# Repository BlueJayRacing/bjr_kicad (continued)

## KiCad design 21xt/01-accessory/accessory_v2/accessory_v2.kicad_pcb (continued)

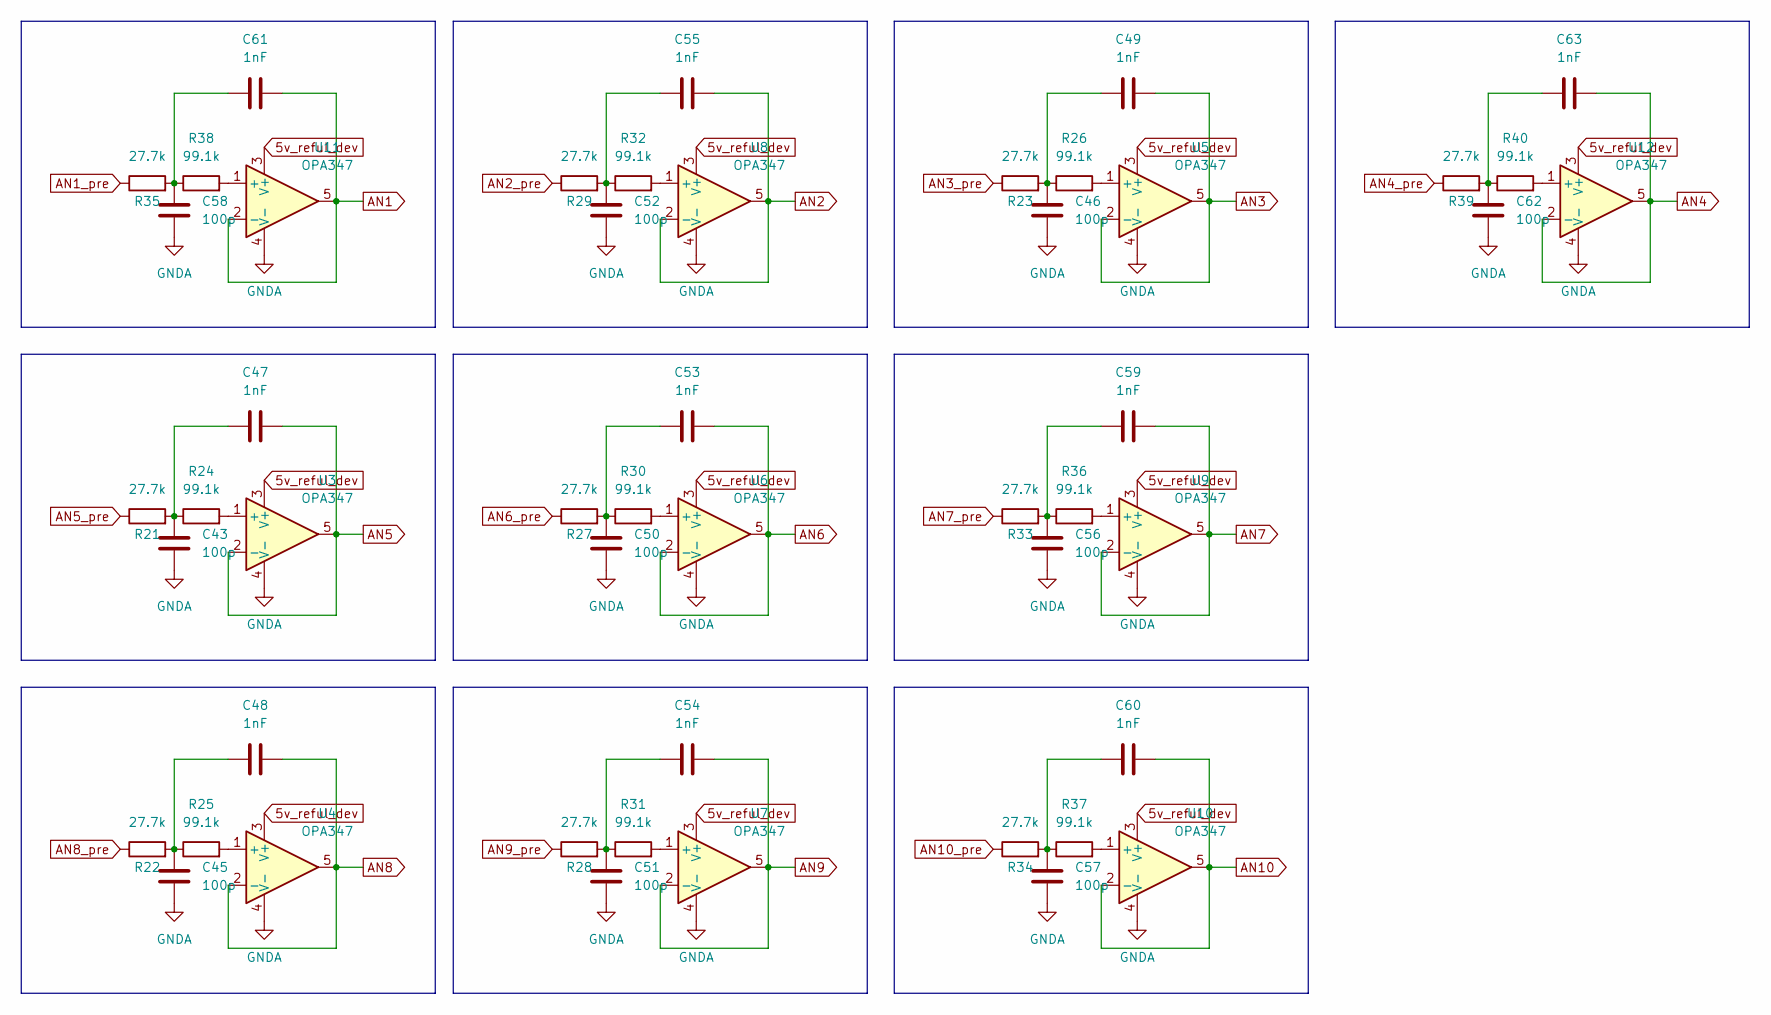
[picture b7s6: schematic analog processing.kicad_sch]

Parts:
C43, C45, C46, C50, C51, C52, C56, C57, C58, C62: 100p; C_0402_1005Metric
C47, C48, C49, C53, C54, C55, C59, C60, C61, C63: 1nF; C_0402_1005Metric
R21, R22, R23, R27, R28, R29, R33, R34, R35, R39: 27.7k; R_0402_1005Metric
R24, R25, R26, R30, R31, R32, R36, R37, R38, R40: 99.1k; R_0402_1005Metric
U3, U4, U5, U6, U7, U8, U9, U10, U11, U12: OPA347; SOT-23-5

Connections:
5v_reful_dev: U3.3 (V+), U4.3 (V+), U5.3 (V+), U6.3 (V+), U7.3 (V+), U8.3 (V+), U9.3 (V+), U10.3 (V+), U11.3 (V+), U12.3 (V+); also elsewhere on the board
AN1: C61.2, U11.2 (-), U11.5; also elsewhere on the board
AN1_pre: R35.1; also elsewhere on the board
AN2: C55.2, U8.2 (-), U8.5; also elsewhere on the board
AN2_pre: R29.1; also elsewhere on the board
AN3: C49.2, U5.2 (-), U5.5; also elsewhere on the board
AN3_pre: R23.1; also elsewhere on the board
AN4: C63.2, U12.2 (-), U12.5; also elsewhere on the board
AN4_pre: R39.1; also elsewhere on the board
AN5: C47.2, U3.2 (-), U3.5; also elsewhere on the board
AN5_pre: R21.1; also elsewhere on the board
AN6: C53.2, U6.2 (-), U6.5; also elsewhere on the board
AN6_pre: R27.1; also elsewhere on the board
AN7: C59.2, U9.2 (-), U9.5; also elsewhere on the board
AN7_pre: R33.1; also elsewhere on the board
AN8: C48.2, U4.2 (-), U4.5; also elsewhere on the board
AN8_pre: R22.1; also elsewhere on the board
AN9: C54.2, U7.2 (-), U7.5; also elsewhere on the board
AN9_pre: R28.1; also elsewhere on the board
AN10: C60.2, U10.2 (-), U10.5; also elsewhere on the board
AN10_pre: R34.1; also elsewhere on the board
unnamed: C43.1, C47.1, R21.2, R24.1
unnamed: C45.1, C48.1, R22.2, R25.1
unnamed: C46.1, C49.1, R23.2, R26.1
unnamed: C50.1, C53.1, R27.2, R30.1
unnamed: C51.1, C54.1, R28.2, R31.1
unnamed: C52.1, C55.1, R29.2, R32.1
unnamed: C56.1, C59.1, R33.2, R36.1
unnamed: C57.1, C60.1, R34.2, R37.1
unnamed: C58.1, C61.1, R35.2, R38.1
unnamed: C62.1, C63.1, R39.2, R40.1
unnamed: R24.2, U3.1 (+)
unnamed: R25.2, U4.1 (+)
unnamed: R26.2, U5.1 (+)
unnamed: R30.2, U6.1 (+)
unnamed: R31.2, U7.1 (+)
unnamed: R32.2, U8.1 (+)
unnamed: R36.2, U9.1 (+)
unnamed: R37.2, U10.1 (+)
unnamed: R38.2, U11.1 (+)
unnamed: R40.2, U12.1 (+)
usb_gnd: C43.2, C45.2, C46.2, C50.2, C51.2, C52.2, C56.2, C57.2, C58.2, C62.2, U3.4 (V-), U4.4 (V-), U5.4 (V-), U6.4 (V-), U7.4 (V-), U8.4 (V-), U9.4 (V-), U10.4 (V-), U11.4 (V-), U12.4 (V-); also elsewhere on the board

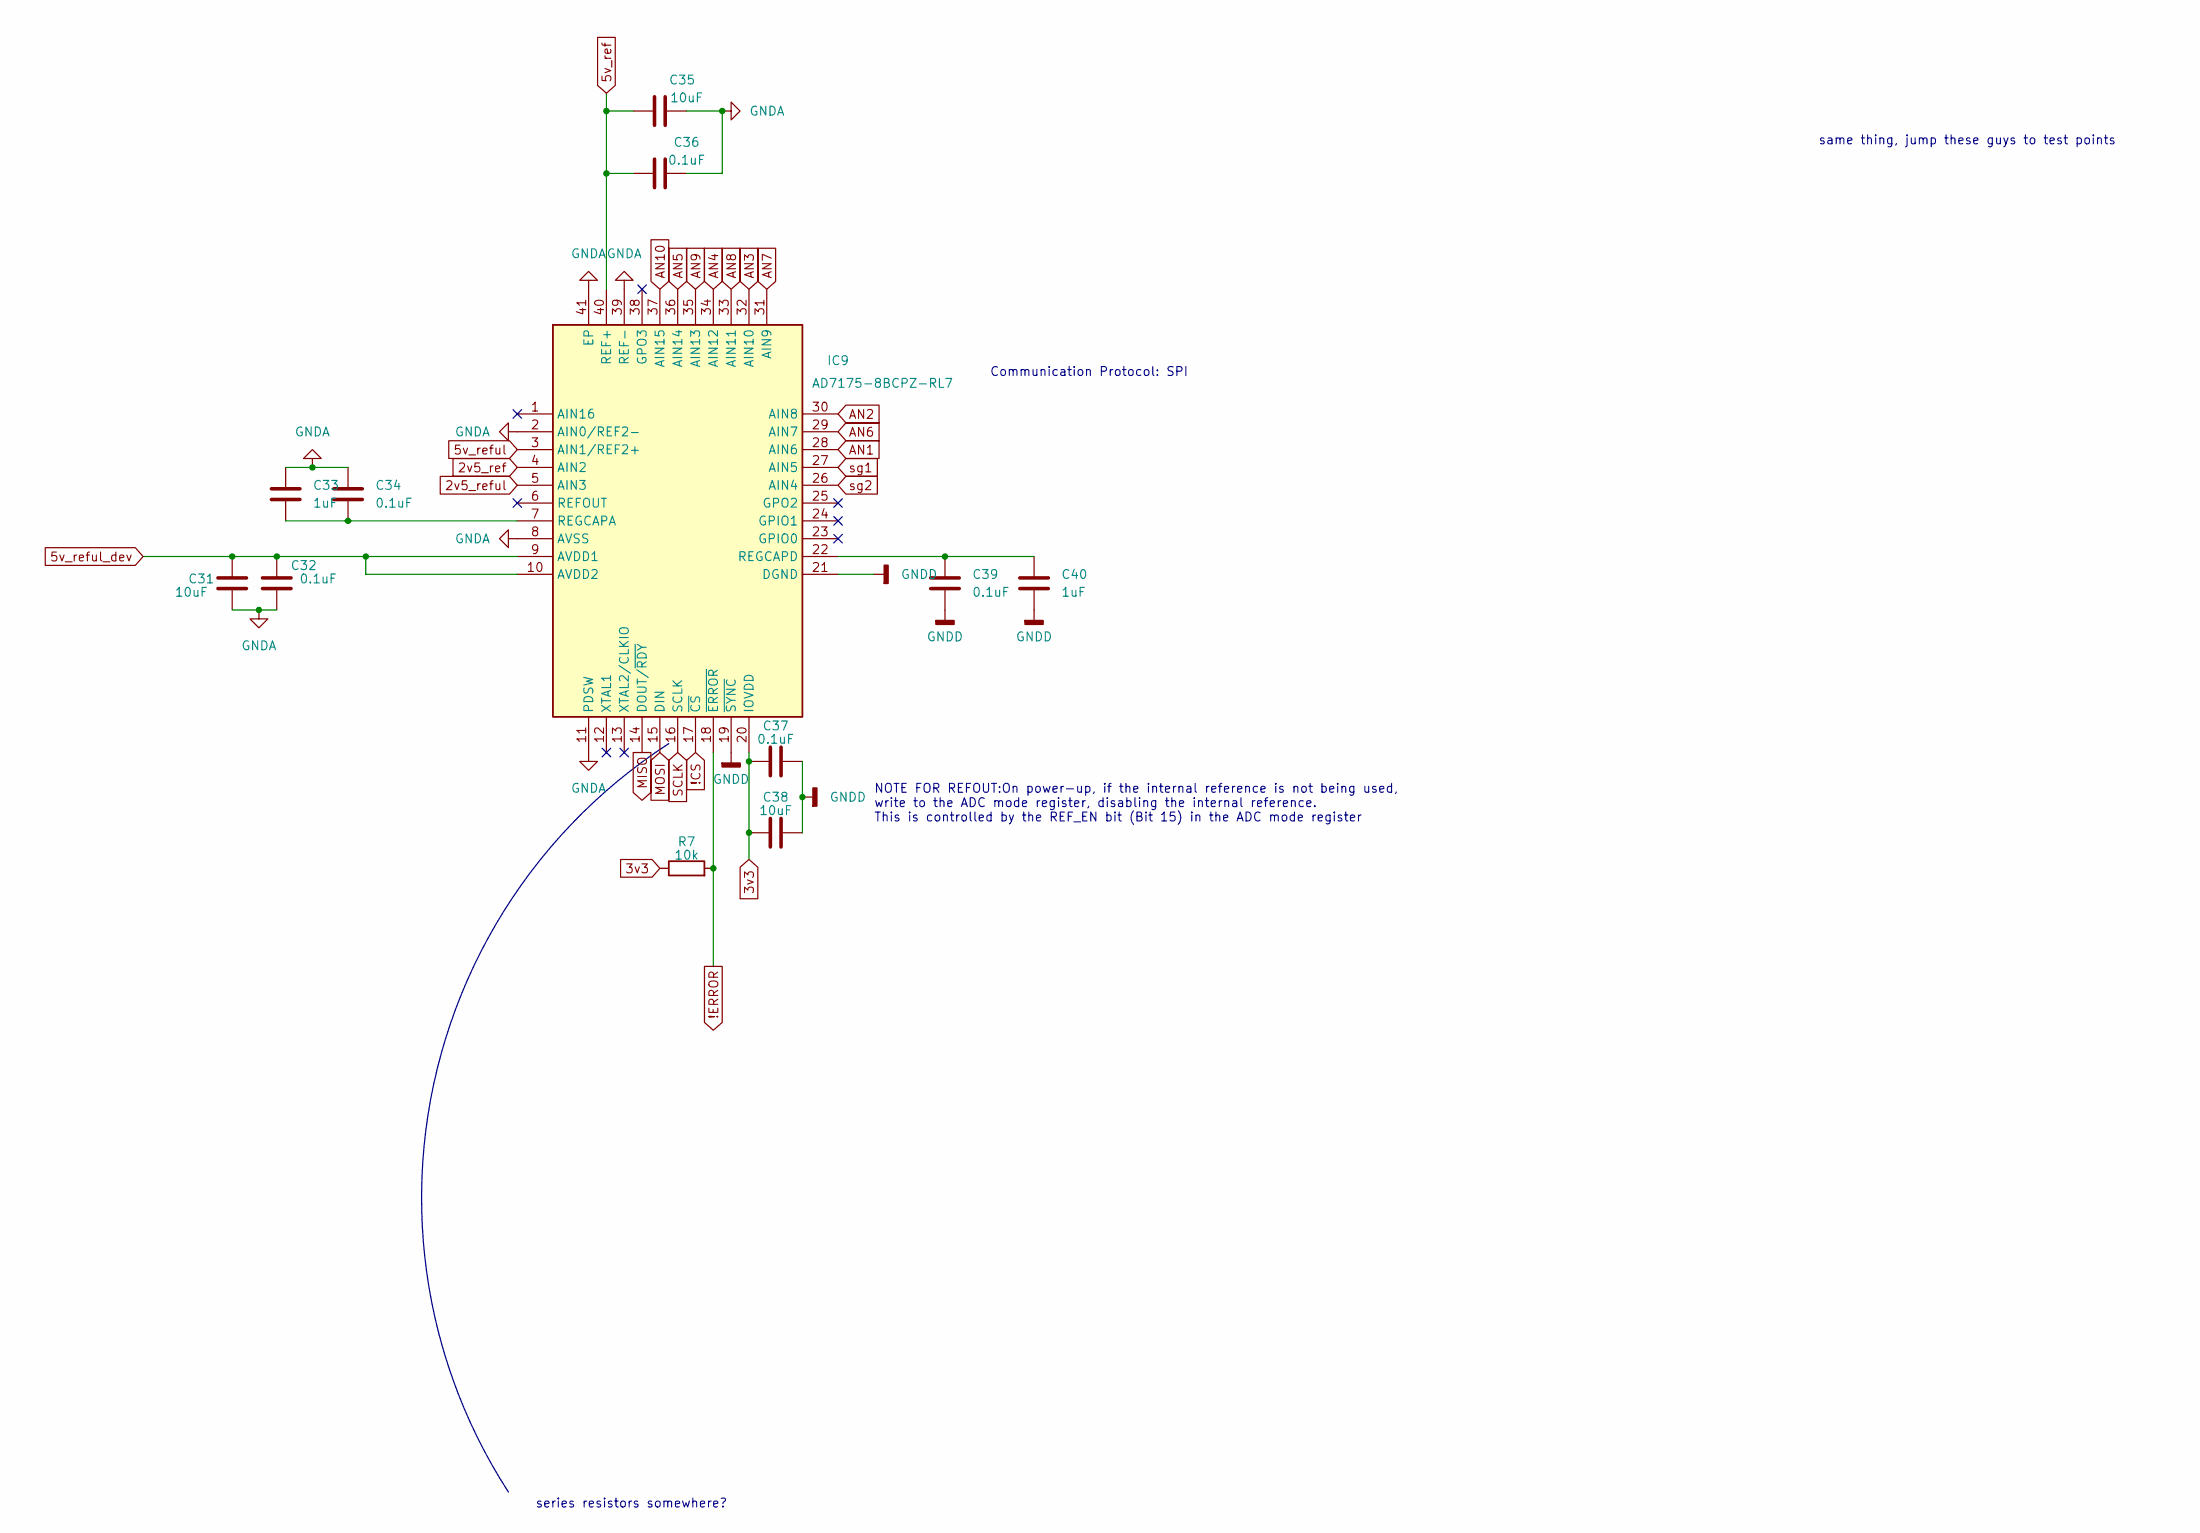
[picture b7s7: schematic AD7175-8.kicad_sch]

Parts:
C31, C35, C38: 10uF; C_0603_1608Metric
C32, C34, C36, C37, C39: 0.1uF; C_0402_1005Metric
C33, C40: 1uF; C_0402_1005Metric
IC9: AD7175-8BCPZ-RL7; Mouser Part Number 584-AD7175-8BCPZ-RL7
R7: 10k; R_0402_1005Metric

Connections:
2v5_ref: IC9.4 (AIN2); also elsewhere on the board
2v5_reful: IC9.5 (AIN3); also elsewhere on the board
3v3: C37.1, C38.1, IC9.20 (IOVDD), R7.1; also elsewhere on the board
5v_ref: C35.1, C36.1, IC9.40 (REF+); also elsewhere on the board
5v_reful: IC9.3 (AIN1/REF2+); also elsewhere on the board
5v_reful_dev: C31.1, C32.1, IC9.9 (AVDD1), IC9.10 (AVDD2); also elsewhere on the board
!CS: IC9.17 (~CS); also elsewhere on the board
!ERROR: IC9.18 (~ERROR), R7.2; also elsewhere on the board
AN1: IC9.28 (AIN6); also elsewhere on the board
AN2: IC9.30 (AIN8); also elsewhere on the board
AN3: IC9.32 (AIN10); also elsewhere on the board
AN4: IC9.34 (AIN12); also elsewhere on the board
AN5: IC9.36 (AIN14); also elsewhere on the board
AN6: IC9.29 (AIN7); also elsewhere on the board
AN7: IC9.31 (AIN9); also elsewhere on the board
AN8: IC9.33 (AIN11); also elsewhere on the board
AN9: IC9.35 (AIN13); also elsewhere on the board
AN10: IC9.37 (AIN15); also elsewhere on the board
MISO: IC9.14 (DOUT/~RDY); also elsewhere on the board
MOSI: IC9.15 (DIN); also elsewhere on the board
unnamed: C33.2, C34.2, IC9.7 (REGCAPA)
unnamed: C39.1, C40.1, IC9.22 (REGCAPD)
SCLK: IC9.16 (SCLK); also elsewhere on the board
sg1: IC9.27 (AIN5); also elsewhere on the board
sg2: IC9.26 (AIN4); also elsewhere on the board
usb_gnd: C31.2, C32.2, C33.1, C34.1, C35.2, C36.2, C37.2, C38.2, C39.2, C40.2, IC9.2 (AIN0/REF2-), IC9.8 (AVSS), IC9.11 (PDSW), IC9.19 (~SYNC), IC9.21 (DGND), IC9.39 (REF-), IC9.41 (EP); also elsewhere on the board

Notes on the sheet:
NOTE FOR REFOUT:On power-up, if the internal reference is not being used, write to the ADC mode register, disabling the internal reference. This is controlled by the REF_EN bit (Bit 15) in the ADC mode register
series resistors somewhere?
Communication Protocol: SPI
same thing, jump these guys to test points

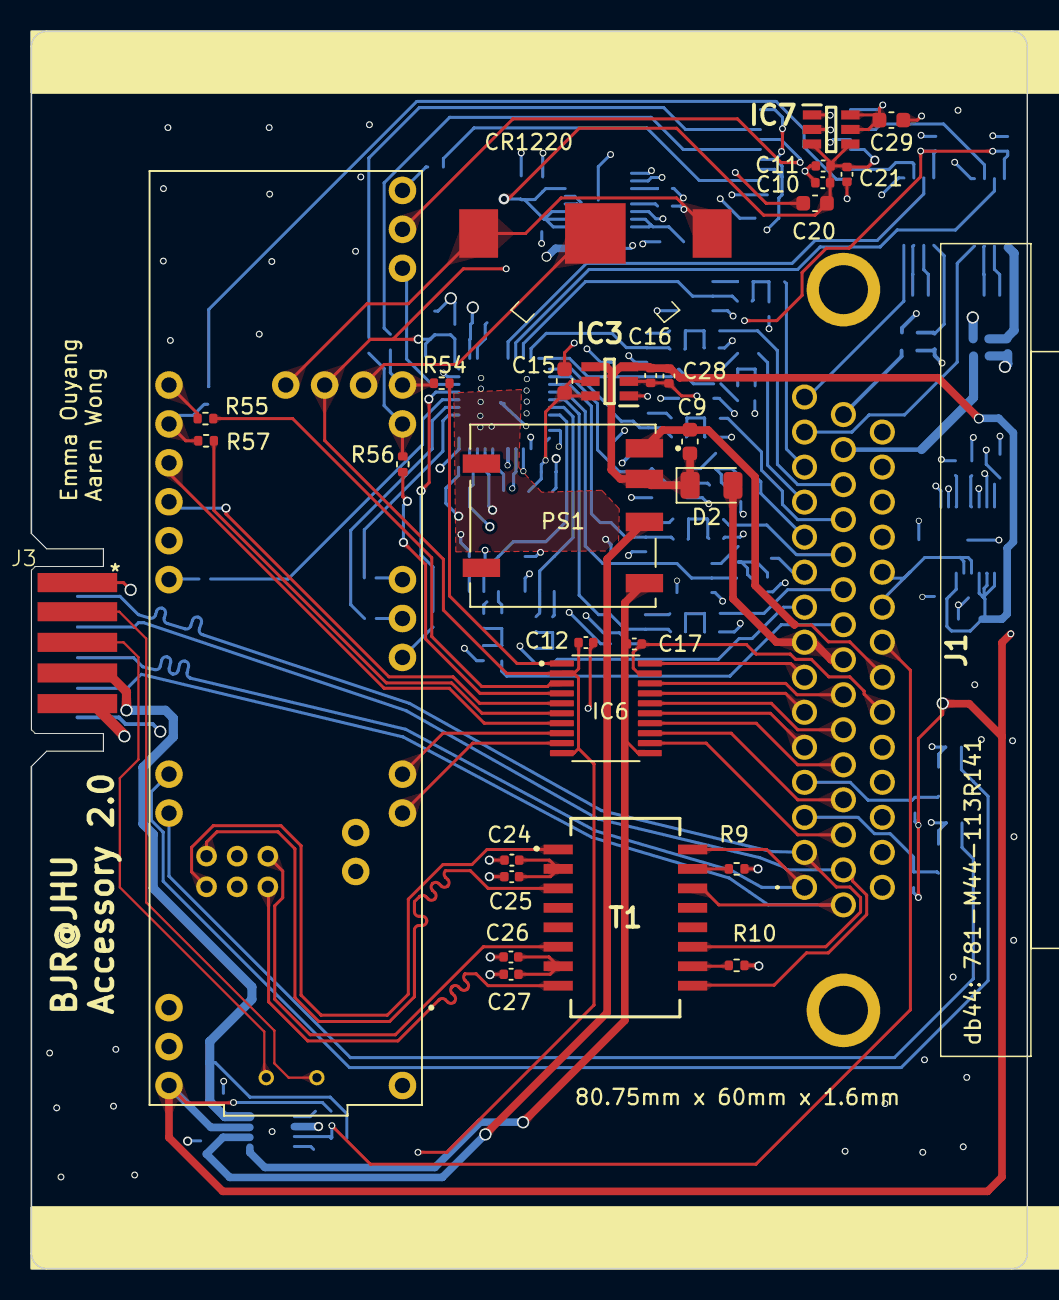
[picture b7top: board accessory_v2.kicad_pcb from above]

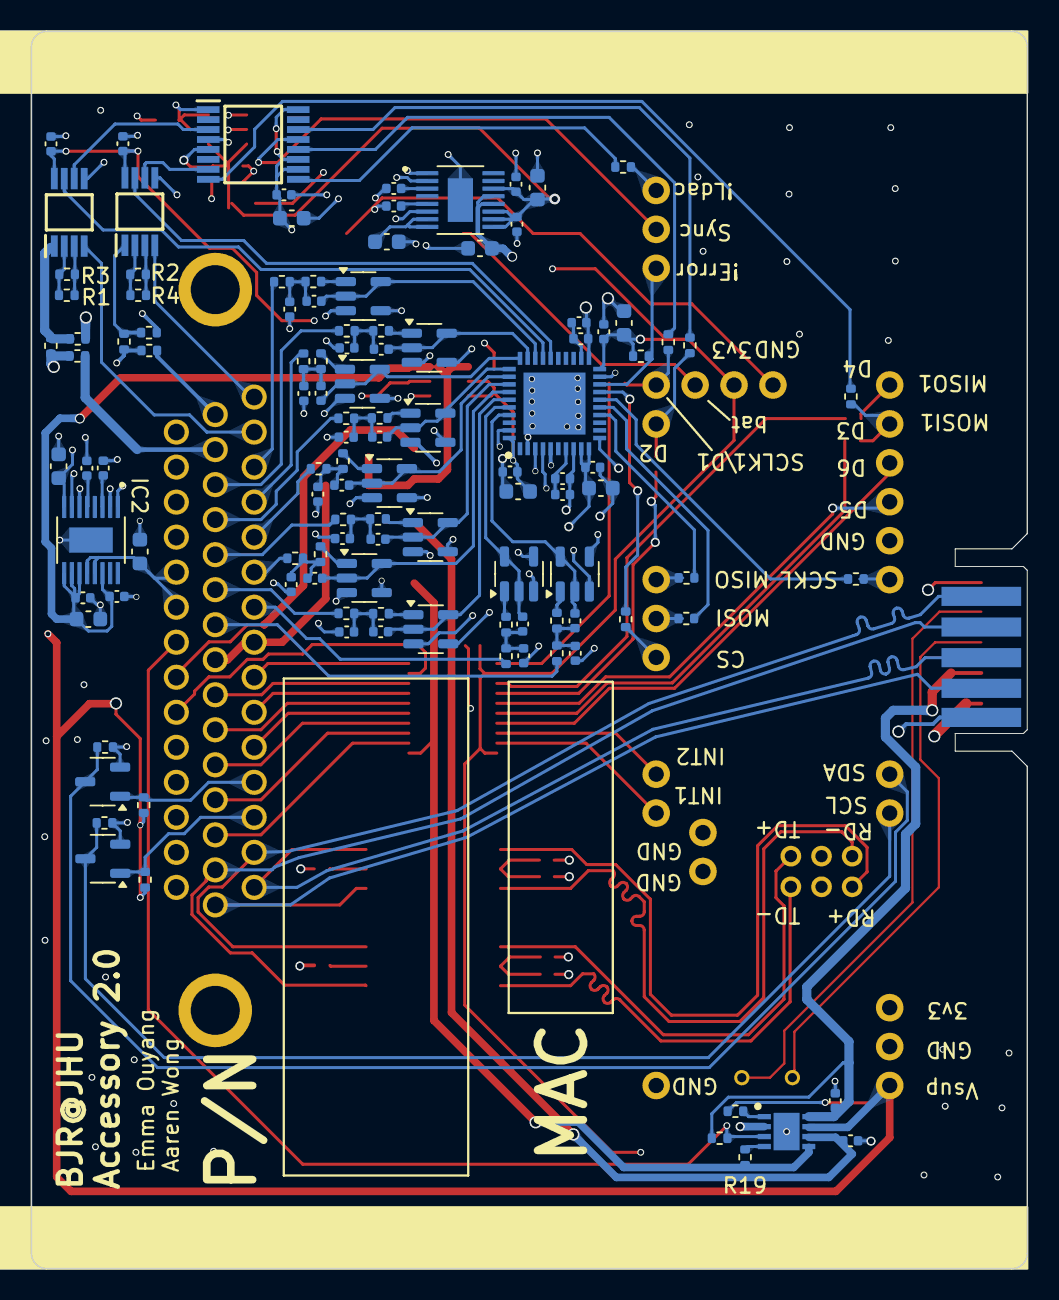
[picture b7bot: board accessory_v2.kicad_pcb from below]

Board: 4 copper layers, 65.0 x 80.8 mm, 146 parts (115 on the bottom side), 131 nets.

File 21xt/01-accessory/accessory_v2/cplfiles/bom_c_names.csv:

Comment,Designator,Footprint,LCSC
"1uF","C1,C5,C11,C14,C19,C28,C33,C40,C44","Capacitor_SMD:C_0402_1005Metric","C52923"
"22uF","C15,C29","Capacitor_SMD:C_0603_1608Metric","C59461"
"0.1uF","C2,C4,C6,C7,C10,C12,C16,C17,C21,C22,C24,C25,C26,C27,C32,C34,C36,C37,C39,C42,C64,C66","Capacitor_SMD:C_0402_1005Metric","C1525"
"10uF","C3,C8,C9,C13,C18,C20,C23,C30,C31,C35,C38,C41","Capacitor_SMD:C_0603_1608Metric","C19702"
"100p","C43,C45,C46,C50,C51,C52,C56,C57,C58,C62","Capacitor_SMD:C_0402_1005Metric","C1546"
"1nF","C47,C48,C49,C53,C54,C55,C59,C60,C61,C63","Capacitor_SMD:C_0402_1005Metric","C1523"
"REF3450IDBVR","IC3","21xt_footprints:REF3450IDBVR","C882410"
"INA821IDGKT","IC4,IC5","21xt_footprints:SOP65P490X110-8N","C2870200"
"TXB0108PWR","IC6","21xt_footprints:SOP65P640X120-20N","C53406"
"REF3425IDBVR","IC7","21xt_footprints:REF3425IDBVR","C187836"
"AD5689RARUZ-RL7","IC8","21xt_footprints:SOP65P640X120-16N","C514225"
"AD7175-8BCPZ-RL7","IC9","21xt_footprints:AD7175-8BCPZ-RL7","C578395"
"NMOS","Q1,Q2","Package_TO_SOT_SMD:SOT-23-3","C112239"
"BSS138","Q3","Package_TO_SOT_SMD:SOT-23-3","C112239"
"5k","R19","Resistor_SMD:R_0402_1005Metric","C25744"
"1k","R20","Resistor_SMD:R_0402_1005Metric","C11702"
"27.7k","R21,R22,R23,R27,R28,R29,R33,R34,R35,R39","Resistor_SMD:R_0402_1005Metric","C25779"
"99.1k","R24,R25,R26,R30,R31,R32,R36,R37,R38,R40","Resistor_SMD:R_0402_1005Metric","C25741"
"20R","R41,R42,R43,R44,R46,R47,R48,R49,R54,R55,R56,R57","Resistor_SMD:R_0402_1005Metric","C4109"
"10k","R5,R6,R7,R11,R12","Resistor_SMD:R_0402_1005Metric","C25744"
"52.5","R9,R10","Resistor_SMD:R_0402_1005Metric","C25120"
"TPS22915BYFPR","U2","21xt_footprints:YFP0004AAAA","C478464"
"OPA347","U3,U4,U5,U6,U7,U8,U9,U10,U11,U12","Package_TO_SOT_SMD:SOT-23-5","C2652269"
